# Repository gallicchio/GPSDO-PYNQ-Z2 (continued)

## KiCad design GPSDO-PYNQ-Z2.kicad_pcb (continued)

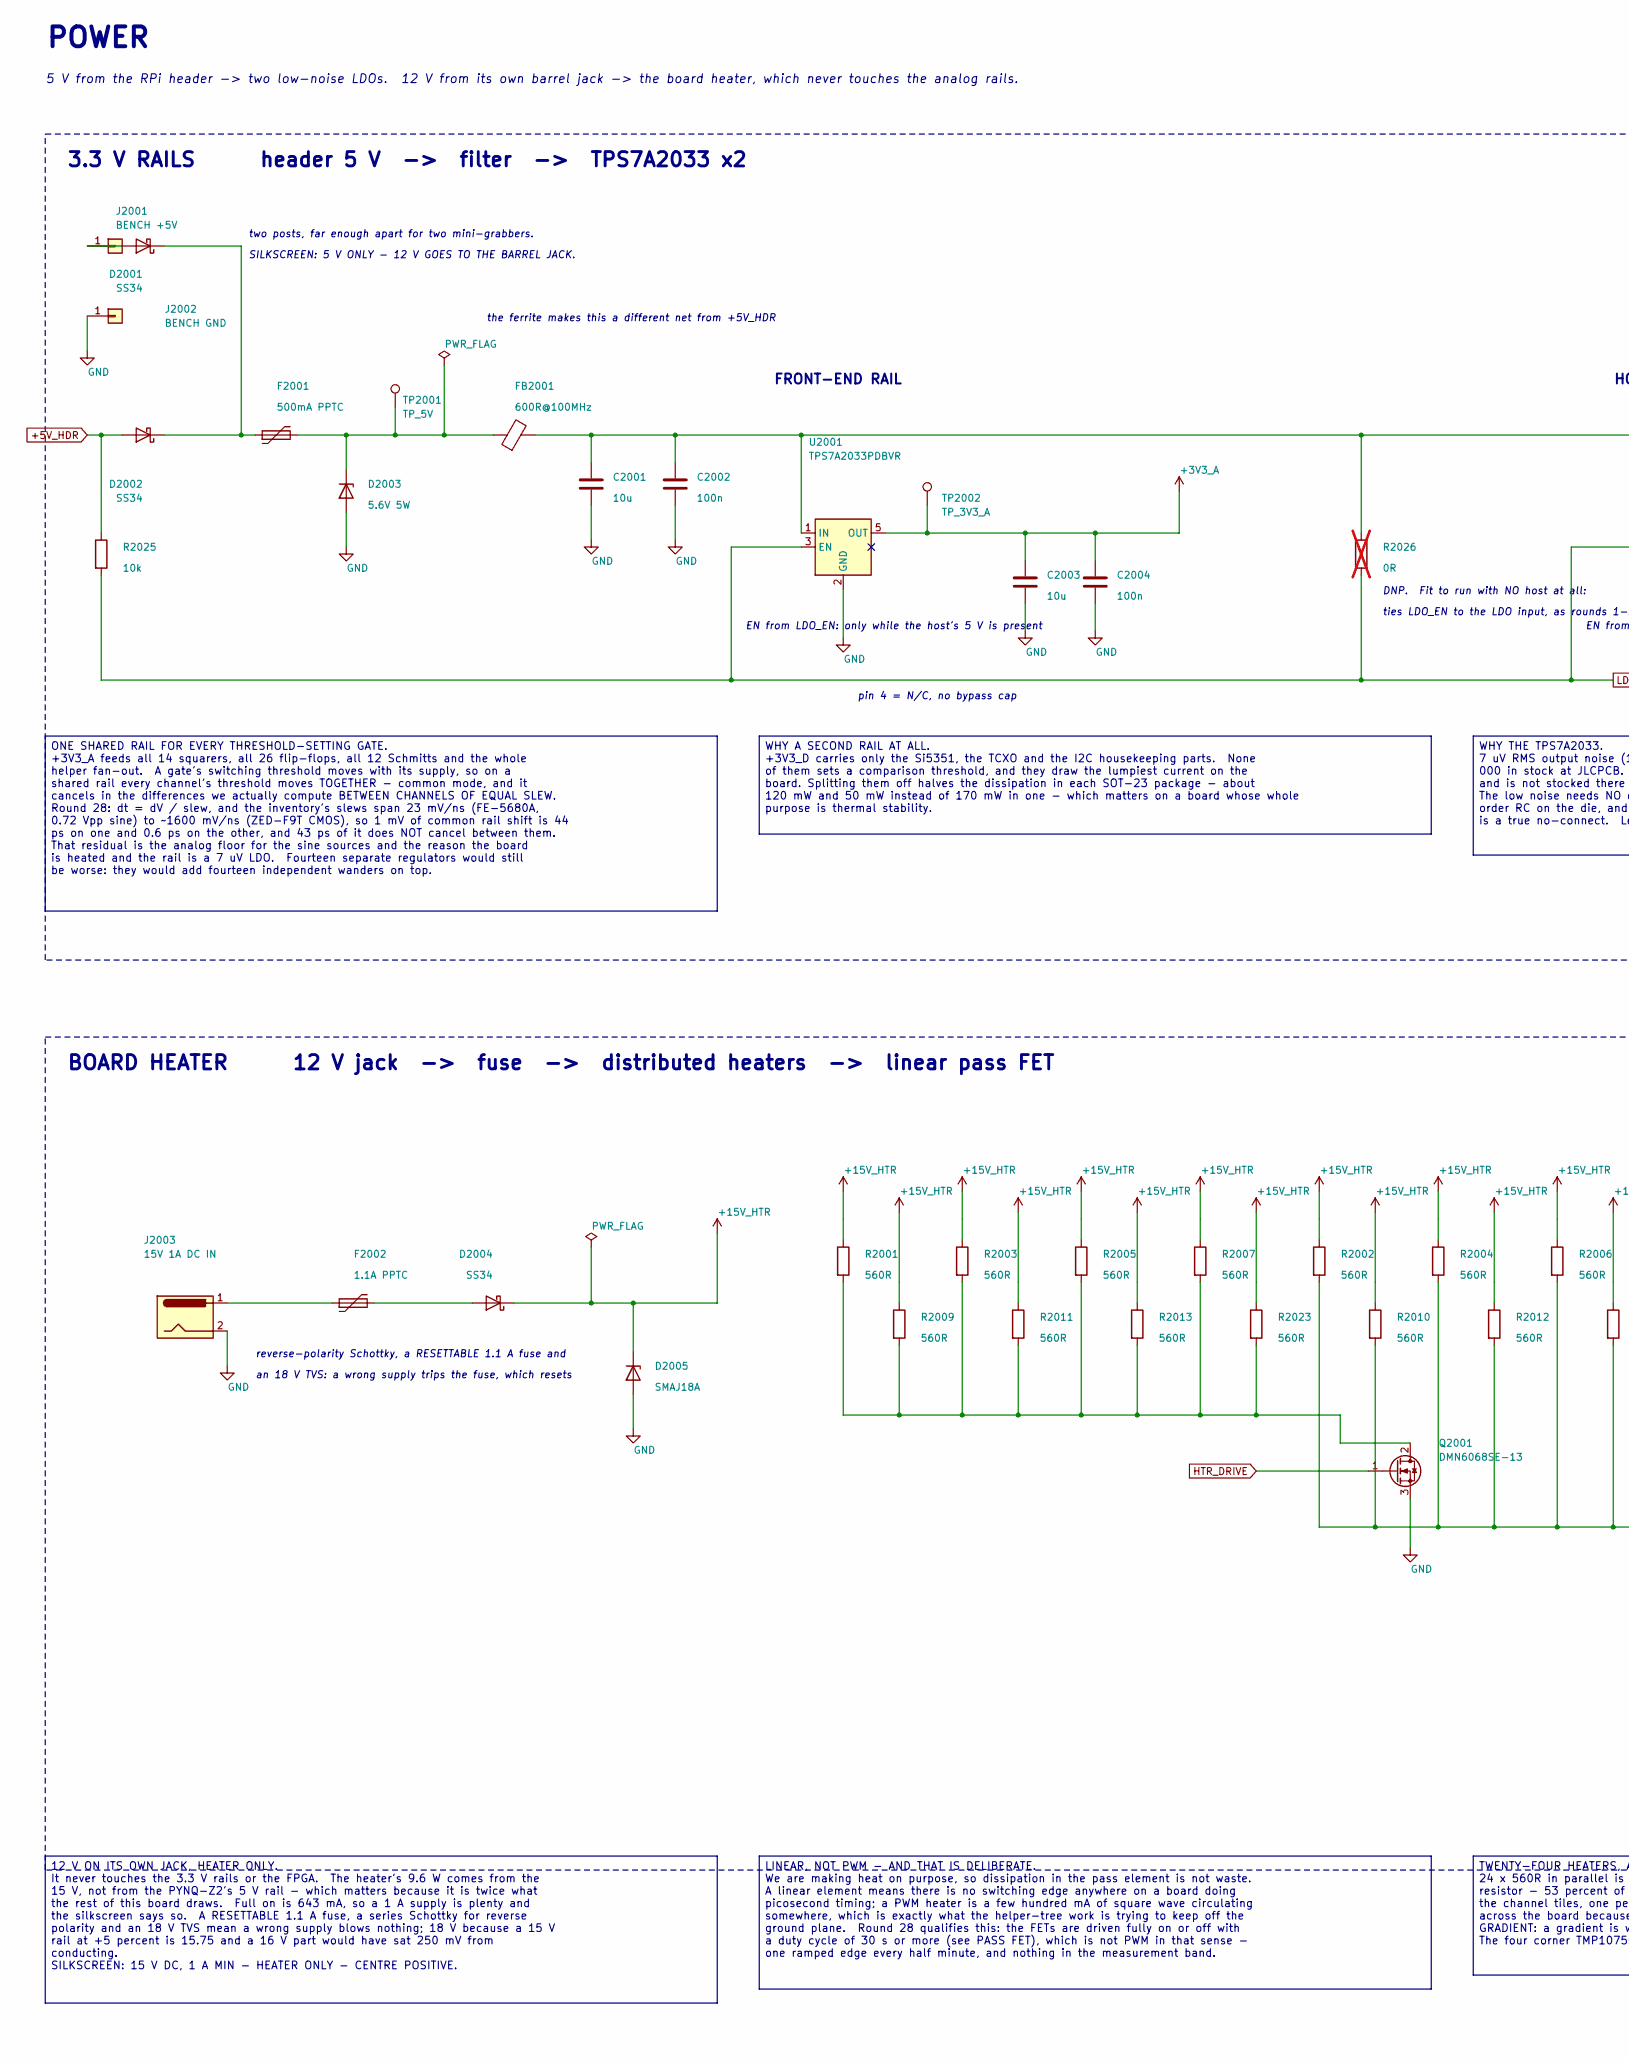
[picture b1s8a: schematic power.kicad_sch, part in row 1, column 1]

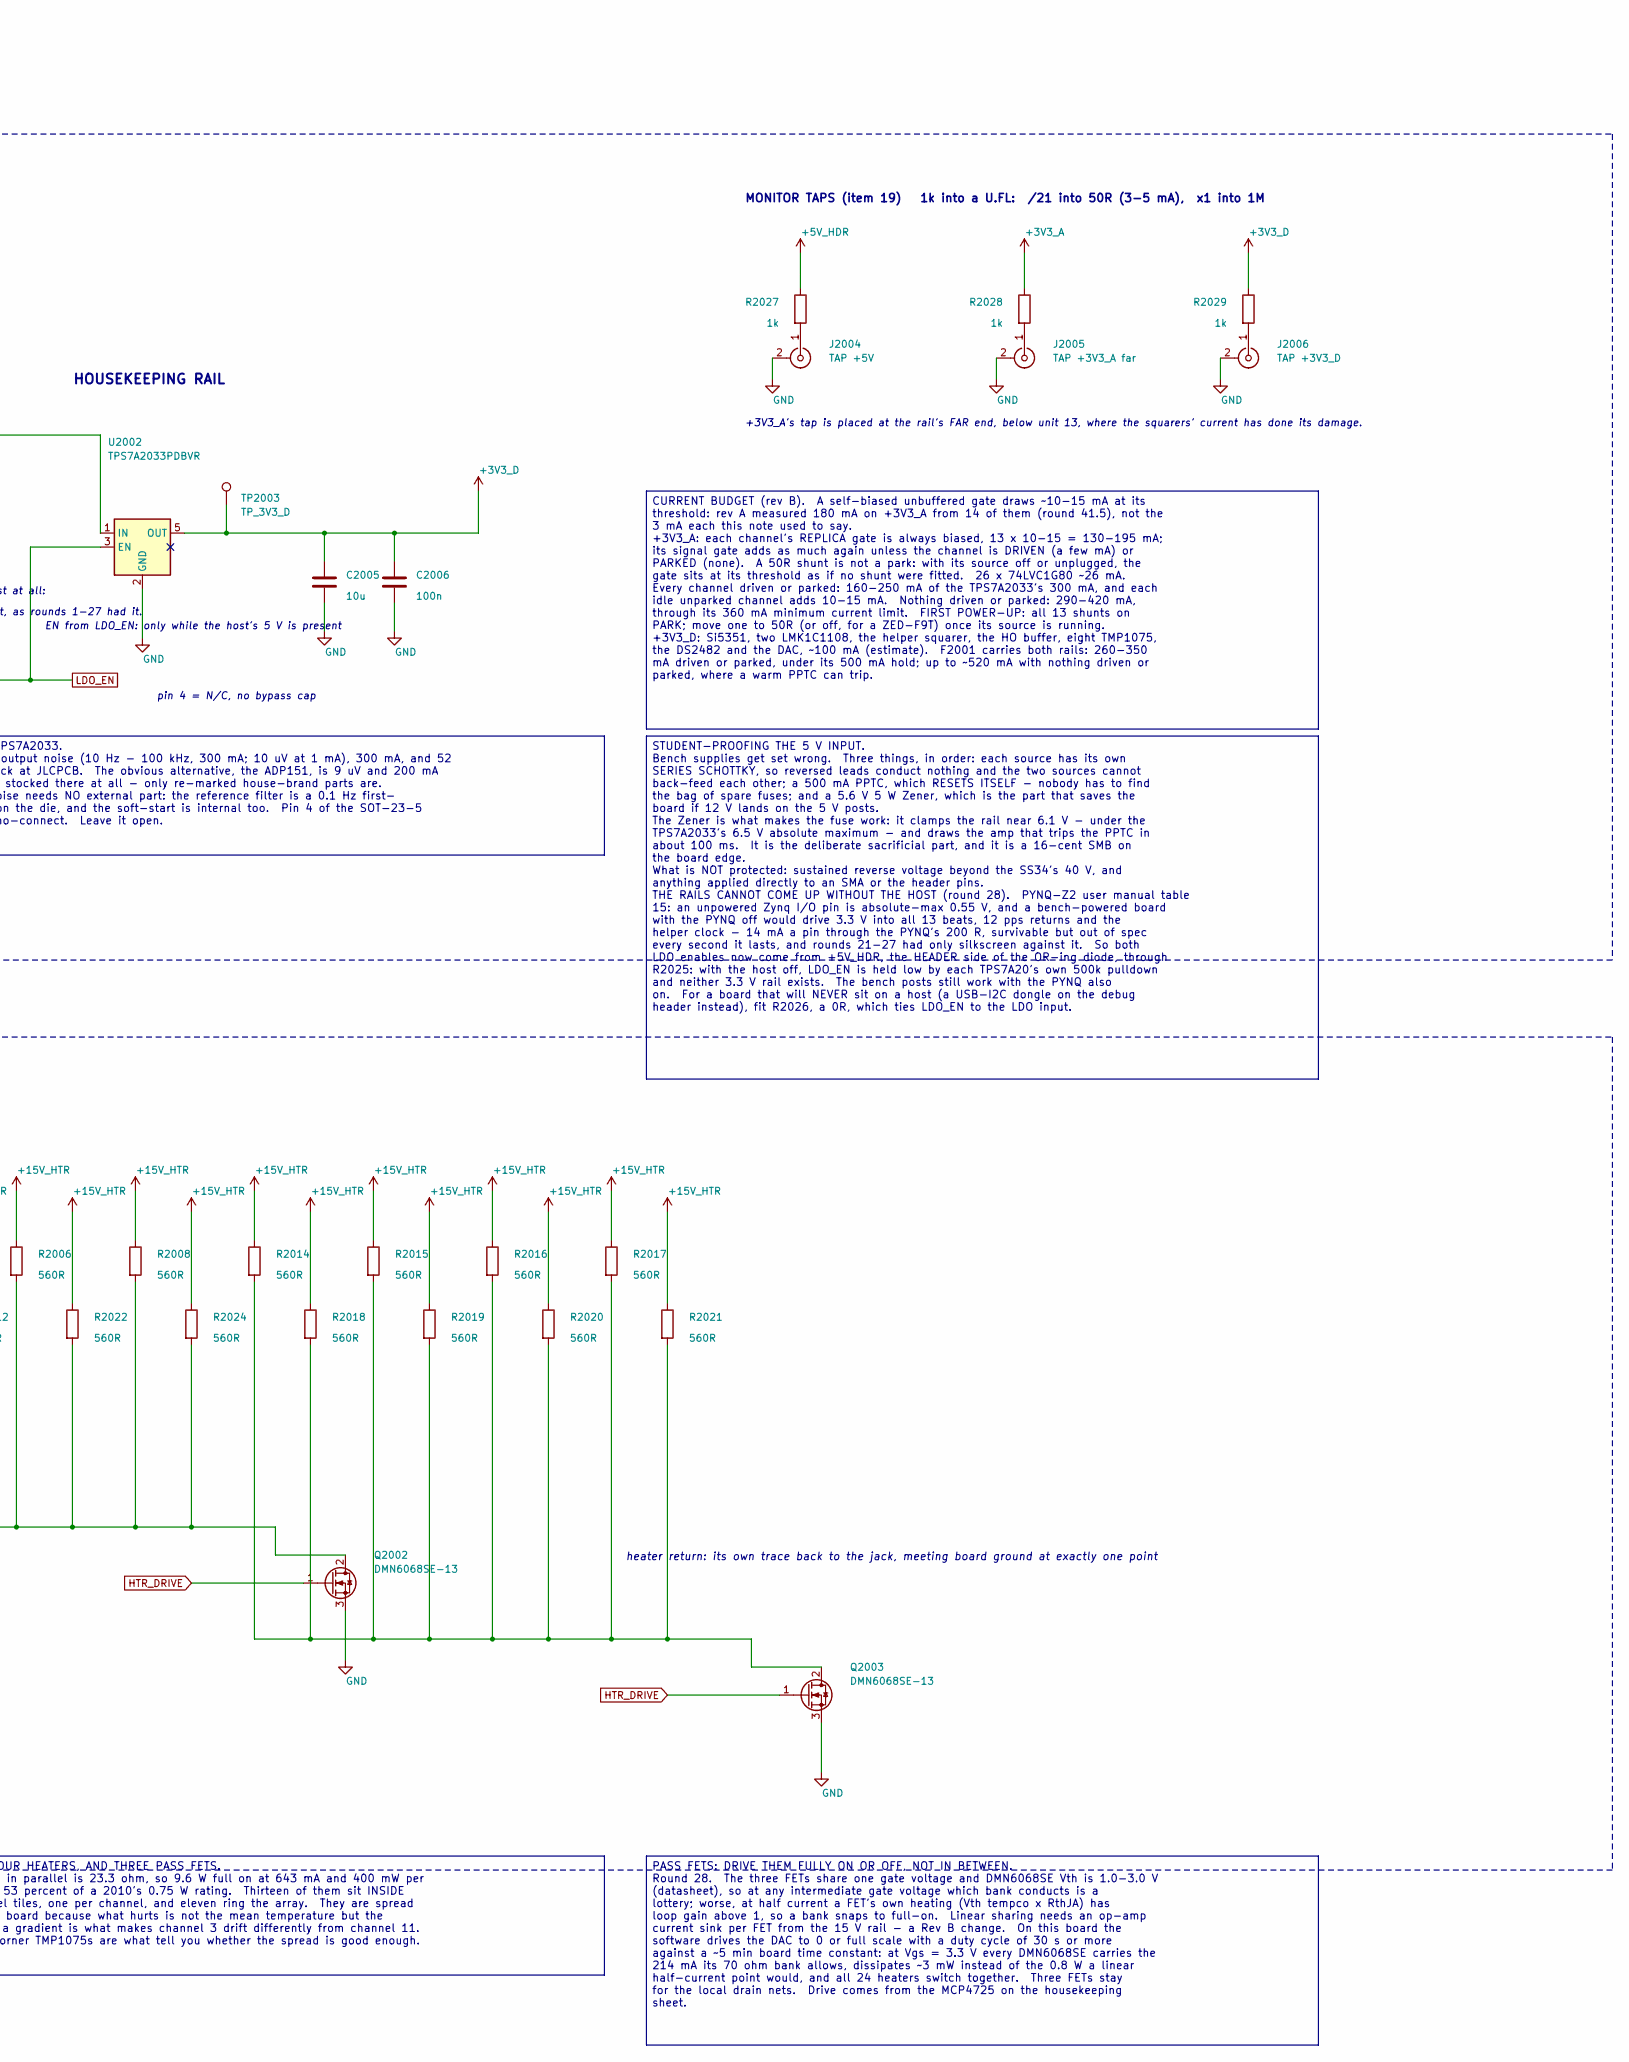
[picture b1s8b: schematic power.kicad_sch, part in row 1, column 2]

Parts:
C2001, C2003, C2005: 10u; C_0805_2012Metric
C2002, C2004, C2006: 100n; C_0805_2012Metric
D2001, D2002, D2004: SS34; D_SMA; LCSC C8678
D2003: 5.6V 5W; D_SMB; LCSC C19077494
D2005: SMAJ18A; D_SMA
F2001: 500mA PPTC; Fuse_1206_3216Metric; LCSC C720075
F2002: 1.1A PPTC; Fuse_1206_3216Metric; LCSC C19108403
FB2001: 600R@100MHz; L_0805_2012Metric
J2001: BENCH +5V; PinHeader_1x01_P2.54mm_Vertical
J2002: BENCH GND; PinHeader_1x01_P2.54mm_Vertical
J2003: 15V 1A DC IN; BarrelJack_Horizontal; LCSC C720557
J2004: TAP +5V; U.FL_Hirose_U.FL-R-SMT-1_Vertical; LCSC C88374
J2005: TAP +3V3_A far; U.FL_Hirose_U.FL-R-SMT-1_Vertical; LCSC C88374
J2006: TAP +3V3_D; U.FL_Hirose_U.FL-R-SMT-1_Vertical; LCSC C88374
Q2001, Q2002, Q2003: DMN6068SE-13; SOT-223-3_TabPin2; LCSC C209902
R2001, R2002, R2003, R2004, R2005, R2006, R2007, R2008, R2009, R2010, R2011, R2012, R2013, R2014, R2015, R2016, R2017, R2018, R2019, R2020, R2021, R2022, R2023, R2024: 560R; R_2010_5025Metric
R2025: 10k; R_0805_2012Metric
R2026: 0R; R_0805_2012Metric; not fitted
R2027, R2028, R2029: 1k; R_0805_2012Metric
TP2001: TP_5V; TestPoint_Pad_D1.5mm
TP2002: TP_3V3_A; TestPoint_Pad_D1.5mm
TP2003: TP_3V3_D; TestPoint_Pad_D1.5mm
U2001, U2002: TPS7A2033PDBVR; SOT-23-5; LCSC C2862740

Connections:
+3V3_A: C2003.1, C2004.1, R2028.1, TP2002.1, U2001.5 (OUT); also elsewhere on the board
+3V3_D: C2005.1, C2006.1, R2029.1, TP2003.1, U2002.5 (OUT); also elsewhere on the board
+5V_HDR: D2002.2 (A), R2025.1, R2027.1; also elsewhere on the board
GND: C2001.2, C2002.2, C2003.2, C2004.2, C2005.2, C2006.2, D2003.2 (A), D2005.2 (A), J2002.1, J2003.2, J2004.2 (Ext), J2005.2 (Ext), J2006.2 (Ext), Q2001.3 (S), Q2002.3 (S), Q2003.3 (S), U2001.2 (GND), U2002.2 (GND); also elsewhere on the board
HTR_DRIVE: Q2001.1 (G), Q2002.1 (G), Q2003.1 (G); also elsewhere on the board
LDO_EN: R2025.2, R2026.2, U2001.3 (EN), U2002.3 (EN)
unnamed: D2001.2 (A), J2001.1
unnamed: D2001.1 (K), D2002.1 (K), F2001.1
unnamed: D2004.2 (A), F2002.2
unnamed: F2002.1, J2003.1
unnamed: J2004.1 (In), R2027.2
unnamed: J2005.1 (In), R2028.2
unnamed: J2006.1 (In), R2029.2
unnamed: Q2001.2 (D), R2001.2, R2003.2, R2005.2, R2007.2, R2009.2, R2011.2, R2013.2, R2023.2
unnamed: Q2002.2 (D), R2002.2, R2004.2, R2006.2, R2008.2, R2010.2, R2012.2, R2022.2, R2024.2
unnamed: Q2003.2 (D), R2014.2, R2015.2, R2016.2, R2017.2, R2018.2, R2019.2, R2020.2, R2021.2
unnamed: C2001.1, C2002.1, FB2001.2, R2026.1, U2001.1 (IN), U2002.1 (IN)

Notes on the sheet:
pin 4 = N/C, no bypass cap
two posts, far enough apart for two mini-grabbers.
SILKSCREEN: 5 V ONLY - 12 V GOES TO THE BARREL JACK.
POWER
5 V from the RPi header -> two low-noise LDOs. 12 V from its own barrel jack -> the board heater, which never touches the analog rails.
+3V3_A's tap is placed at the rail's FAR end, below unit 13, where the squarers' current has done its damage.
an 18 V TVS: a wrong supply trips the fuse, which resets
EN from LDO_EN: only while the host's 5 V is present
3.3 V RAILS header 5 V -> filter -> TPS7A2033 x2
DNP. Fit to run with NO host at all:
reverse-polarity Schottky, a RESETTABLE 1.1 A fuse and
MONITOR TAPS (item 19) 1k into a U.FL: /21 into 50R (3-5 mA), x1 into 1M
HOUSEKEEPING RAIL
heater return: its own trace back to the jack, meeting board ground at exactly one point
the ferrite makes this a different net from +5V_HDR
FRONT-END RAIL
ties LDO_EN to the LDO input, as rounds 1-27 had it.
BOARD HEATER 12 V jack -> fuse -> distributed heaters -> linear pass FET
CURRENT BUDGET (rev B). A self-biased unbuffered gate draws ~10-15 mA at its threshold: rev A measured 180 mA on +3V3_A from 14 of them (round 41.5), not the 3 mA each this note used to say. +3V3_A: each channel's REPLICA gate is always biased, 13 x 10-15 = 130-195 mA; its signal gate adds as much 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
PASS FETS: DRIVE THEM FULLY ON OR OFF, NOT IN BETWEEN. Round 28. The three FETs share one gate voltage and DMN6068SE Vth is 1.0-3.0 V (datasheet), so at any intermediate gate voltage which bank conducts is a lottery; worse, at half current a FET's own heating (Vth tempco x RthJA) has loop gain abov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
TWENTY-FOUR HEATERS, AND THREE PASS FETS. 24 x 560R in parallel is 23.3 ohm, so 9.6 W full on at 643 mA and 400 mW per resistor - 53 percent of a 2010's 0.75 W rating. Thirteen of them sit INSIDE the channel tiles, one per channel, and eleven ring the array. They are spread across the board because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
LINEAR, NOT PWM - AND THAT IS DELIBERATE. We are making heat on purpose, so dissipation in the pass element is not waste. A linear element means there is no switching edge anywhere on a board doing picosecond timing; a PWM heater is a few hundred mA of square wave circulating somewhere, which is ex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
STUDENT-PROOFING THE 5 V INPUT. Bench supplies get set wrong. Three things, in order: each source has its own SERIES SCHOTTKY, so reversed leads conduct nothing and the two sources cannot back-feed each other; a 500 mA PPTC, which RESETS ITSELF - nobody has to find the bag of spare fuses; and a 5.6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
ONE SHARED RAIL FOR EVERY THRESHOLD-SETTING GATE. +3V3_A feeds all 14 squarers, all 26 flip-flops, all 12 Schmitts and the whole helper fan-out. A gate's switching threshold moves with its supply, so on a shared rail every channel's threshold moves TOGETHER - common mode, and it cancels in the diff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
WHY THE TPS7A2033. 7 uV RMS output noise (10 Hz - 100 kHz, 300 mA; 10 uV at 1 mA), 300 mA, and 52 000 in stock at JLCPCB. The obvious alternative, the ADP151, is 9 uV and 200 mA and is not stocked there at all - only re-marked house-brand parts are. The low noise needs NO external part: the referen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
WHY A SECOND RAIL AT ALL. +3V3_D carries only the Si5351, the TCXO and the I2C housekeeping parts. None of them sets a comparison threshold, and they draw the lumpiest current on the board. Splitting them off halves the dissipation in each SOT-23 package - about 120 mW and 50 mW instead of 170 mW i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
12 V ON ITS OWN JACK, HEATER ONLY. It never touches the 3.3 V rails or the FPGA. The heater's 9.6 W comes from the 15 V, not from the PYNQ-Z2's 5 V rail - which matters because it is twice what the rest of this board draws. Full on is 643 mA, so a 1 A supply is plenty and the silkscreen says so. A 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

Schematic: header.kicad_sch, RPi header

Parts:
J4001: 2x20 socket 2.54mm; RPiHeader_2x20_Socket_Underside; LCSC C2977589

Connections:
+5V_HDR: J4001.2, J4001.4; also elsewhere on the board
BEAT_00: J4001.23; also elsewhere on the board
BEAT_01: J4001.7; also elsewhere on the board
BEAT_02: J4001.27; also elsewhere on the board
BEAT_03: J4001.11; also elsewhere on the board
BEAT_04: J4001.29; also elsewhere on the board
BEAT_05: J4001.13; also elsewhere on the board
BEAT_06: J4001.31; also elsewhere on the board
BEAT_07: J4001.15; also elsewhere on the board
BEAT_08: J4001.33; also elsewhere on the board
BEAT_09: J4001.19; also elsewhere on the board
BEAT_10: J4001.35; also elsewhere on the board
BEAT_11: J4001.21; also elsewhere on the board
BEAT_12: J4001.37; also elsewhere on the board
GND: J4001.6, J4001.9, J4001.14, J4001.20, J4001.25, J4001.30, J4001.34, J4001.39; also elsewhere on the board
HELPER_CLK: J4001.18; also elsewhere on the board
I2C_SCL: J4001.5; also elsewhere on the board
I2C_SDA: J4001.3; also elsewhere on the board
PPS_00: J4001.26; also elsewhere on the board
PPS_01: J4001.8; also elsewhere on the board
PPS_02: J4001.28; also elsewhere on the board
PPS_03: J4001.10; also elsewhere on the board
PPS_04: J4001.32; also elsewhere on the board
PPS_05: J4001.12; also elsewhere on the board
PPS_06: J4001.36; also elsewhere on the board
PPS_07: J4001.16; also elsewhere on the board
PPS_08: J4001.38; also elsewhere on the board
PPS_09: J4001.22; also elsewhere on the board
PPS_10: J4001.40; also elsewhere on the board
PPS_11: J4001.24; also elsewhere on the board

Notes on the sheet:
C20 IO_L1P_T0_AD0P_35 unit 6 pps
B20 IO_L1N_T0_AD0N_35 unit 5 pps
pin 1 3V3 from the host - NOT CONNECTED
U19 IO_L12N_T1_MRCC_34 unit 1 pps
W9 IO_L16N_T2_13 unit 13 beat
V6 IO_L22P_T3_13 unit 2 pps
Y16 IO_L7P_T1_34 unit 3 beat
F19 IO_L15P_T2_DQS_AD12P_35 unit 12 pps
U8 IO_L17N_T2_13 unit 8 beat
W8 IO_L15N_T2_DQS_13 unit 9 beat
V7 IO_L11N_T1_SRCC_13 unit 6 beat
Y18 IO_L17P_T2_34 unit 2 beat
V8 IO_L15P_T2_DQS_13 unit 10 beat
Y9 IO_L14P_T2_SRCC_13 unit 11 pps
2x20 female socket on the underside. Pin map taken from TUL_PYNQ_Schematic_R12.pdf sheet 4, cross-checked against Vivado's PIN_FUNC database. Every signal pin has its own 200R series resistor on the PYNQ-Z2.
Y6 IO_L13N_T2_MRCC_13 unit 4 pps
W10 IO_L16P_T2_13 unit 1 beat
V10 IO_L21N_T3_DQS_13 unit 12 beat
W18 IO_L22P_T3_34 I2C SDA - 2k2 pull-up already on PYNQ-Z2
pin 17 3V3 from the host - NOT CONNECTED
Y19 IO_L17N_T2_34 unit 5 beat
U18 IO_L12P_T1_MRCC_34 unit 7 beat
Y8 IO_L14N_T2_SRCC_13 unit 11 beat
U7 IO_L11P_T1_SRCC_13 unit 4 beat
F20 IO_L15N_T2_DQS_AD12N_35 unit 10 pps
Y7 IO_L13P_T2_MRCC_13 HELPER CLOCK -> FPGA (MRCC P, bank 13)
A20 IO_L2N_T0_AD8N_35 unit 9 pps
W19 IO_L22N_T3_34 I2C SCL - 2k2 pull-up already on PYNQ-Z2
B19 IO_L2P_T0_AD8P_35 unit 7 pps
RASPBERRY PI 40-PIN HEADER
W6 IO_L22N_T3_13 unit 8 pps
Y17 IO_L7N_T1_34 unit 3 pps
NO MODIFICATION TO THE PYNQ-Z2 IS NEEDED - BUT PMOD A BECOMES UNUSABLE. This board is designed for a stock PYNQ-Z2. It relies on the 200 ohm series resistor the PYNQ puts in every Raspberry Pi GPIO, and on the 2k2 I2C pull-ups above; both are fitted from the factory and neither should be removed. W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
THE ROW SPLIT IS NOT A COINCIDENCE. After taking pins 3 and 5 for I2C the odd row has exactly 13 signal pins left, and after taking pin 18 for the helper the even row has exactly 12. So every BEAT is on the odd row and every PPS on the even row, which separates the two families across the connector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
THE HELPER GOES IN ON PIN 18. Y7 = rpio_24 = IO_L13P_T2_MRCC_13: an MRCC P-side pin in bank 13, the best clock input on the board. The same physical pin is a dedicated PCLKT6_1 primary clock input on an Icepi Zero, so one choice serves both platforms. Pin 31 (U18, MRCC bank 34) is the fallback.
PIN 1 AND PIN 17 ARE LEFT UNCONNECTED. Both are the host's 3.3 V. We make our own 3.3 V from the header's 5 V, and not bridging to the host's rail means we cannot back-feed it. The TUL user manual's Table 22 shows pin 1 as GROUND; the schematic shows 3V3, and the schematic is right. Leaving the pin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
PIN 13 IS REAL AND IS MISSING FROM THE STOCK XDC. Net RPIO_27_R, package pin V7, IO_L11N_T1_SRCC_13, fed through R87 (200R 1%). The widely-circulated pynq-z2.xdc simply omits it, so anyone counting from that file finds 26 usable pins where the board has 28. On this board it carries BEAT_05. Add the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
2k2 PULL-UPS ARE ALREADY FITTED ON THE PYNQ-Z2 on header pins 3, 5, 27 and 28 (R305-R308), which is the standard Raspberry Pi I2C arrangement. Do not add more on this board. Pins 27 and 28 carry BEAT_02 and PPS_02; a 2k2 pull-up on a push-pull LVC output is 1.5 mA and harmless, and any rise/fall as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

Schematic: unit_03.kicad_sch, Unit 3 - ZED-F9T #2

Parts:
C301: 10n C0G; C_0805_2012Metric
C302, C304, C306, C308: 100n; C_0805_2012Metric
C303, C305, C307, C309: 10n; C_0805_2012Metric
D301: BAV99; SOT-23; LCSC C916421; not fitted
J301: 10MHz IN; SMA_Vertical_THT_Universal; LCSC C496549
J302: 1pps IN; SMA_Vertical_THT_Universal; LCSC C496549
J303: TAP IN; U.FL_Hirose_U.FL-R-SMT-1_Vertical; LCSC C88374
J304: TAP SQ; U.FL_Hirose_U.FL-R-SMT-1_Vertical; LCSC C88374
JP301: 50R/PARK; PinHeader_1x03_P2.54mm_Vertical
R301: 51R 1%; R_0805_2012Metric
R302: 0R; R_0805_2012Metric
R303: 2k2; R_0805_2012Metric
R304: 330R; R_0805_2012Metric
R305: 1M 1%; R_0805_2012Metric
R306: 51R; R_0805_2012Metric; not fitted
R307, R321, R323: 1k; R_0805_2012Metric
R308: 10k; R_0805_2012Metric
R322: 100k; R_0805_2012Metric
R351, R352, R353, R354: 4R7; R_0805_2012Metric
TP301: TP_IN; TestPoint_Pad_D1.5mm
TP302: TP_SQ; TestPoint_Pad_D1.5mm
TP303: TP_BEAT; TestPoint_Pad_D1.5mm
TP304: TP_PPS; TestPoint_Pad_D1.5mm
U301: 74LVC2GU04; SOT-363_SC-70-6; LCSC C116660
U302, U303: 74LVC1G80; SOT-23-5; LCSC C42879
U304: 74LVC1G17; SOT-23-5; LCSC C7836

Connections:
+3V3_A: D301.1 (K), R351.1, R352.1, R353.1, R354.1; also elsewhere on the board
/Unit 03/PARK: JP301.3, R322.2
/Unit 03/REPLICA: R305.2, U301.3 (2A), U301.4 (2Y)
BEAT_02: TP303.1, U303.4 (~Q); also elsewhere on the board
GND: C302.2, C303.2, C304.2, C305.2, C306.2, C307.2, C308.2, C309.2, D301.2 (A), J301.2 (Ext), J302.2 (Ext), J303.2 (Ext), J304.2 (Ext), JP301.2, R303.2, R306.2, R308.2, U301.2 (GND), U302.3 (GND), U303.3 (GND), U304.3 (GND); also elsewhere on the board
HCLK_02: U302.2 (C), U303.2 (C); also elsewhere on the board
unnamed: C301.1, R302.2, R303.1, R321.2
unnamed: C301.2, D301.3 (K), R304.1
unnamed: J301.1 (In), R301.1, R302.1, TP301.1
unnamed: J302.1 (In), R306.1, R307.1
unnamed: J303.1 (In), R321.1
unnamed: J304.1 (In), R323.1
unnamed: JP301.1, R301.2
unnamed: R307.2, R308.1, U304.2
unnamed: R304.2, R305.1, R322.1, TP302.1, U301.1 (1A)
unnamed: R323.2, U301.6 (1Y), U302.1 (D)
unnamed: C302.1, C303.1, R351.2, U301.5 (VCC)
unnamed: C304.1, C305.1, R352.2, U302.5 (VCC)
unnamed: U302.4 (~Q), U303.1 (D)
unnamed: C306.1, C307.1, R353.2, U303.5 (VCC)
unnamed: C308.1, C309.1, R354.2, U304.5 (VCC)
PPS_02: TP304.1, U304.4; also elsewhere on the board

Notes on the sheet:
UNIT 3 - ZED-F9T #2
out: PPS_02, one rising edge per second, 0/3.3 V, straight to the RPi header
bounds the current from a
DC level when nothing
neither = a driven, unterminated input
1k/10k suits a 3.3 V and a 5 V
10 MHz DDMTD front end + 1 pps front end. Every unit sheet has this same layout; only the names, the per-channel population and the expected levels differ.
1 pps CHANNEL divide -> Schmitt -> straight to the FPGA
10 MHz DDMTD CHANNEL terminate -> AC couple -> square -> sample -> retime
supply pin: it decides at its threshold, not 70 mV off (item 18).
AC couple
1-2 = 50 ohm terminate (ON except ZED-F9T)
jumper is off, and sets the
DNP: nothing here drives 50 ohm
is plugged in
OUT BEAT_02 -> sheet 'RPi header' OUT PPS_02 -> sheet 'RPi header' IN HELPER_FANOUT <- sheet 'Helper'
HCLK_02: 10.0012 MHz, 0/3.3 V, this channel's own length-matched branch off the fan-out
its own threshold; the 1M carries that to half 1. One die, one
2-3 = PARK: source off or unplugged (not 50R)
REPLICA BIAS. Half 2, its input tied to its output, sits at
pps alike, so no channel differs
high-Z source when the
into FF1.D: 0/3.3 V CMOS at 10 MHz, edges ~1-2 ns
out of FF2: BEAT_02, ~1234 Hz square, 0/3.3 V - its EDGE TIME is the measurement
DNP clamp: fit only for an unterminated hot source
THE SAMPLING FLIP-FLOP (FF1) IS DELIBERATELY ALLOWED TO GO METASTABLE - that is measurement. Never put a synchronizer in front of it. THE RETIMER (FF2) re-clocks on the next helper edge, so what leaves the board is always a clean transition aligned to a helper edge. It costs exactly one helper cycl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
AT THE INPUT NODE, before the coupling cap 3.30 Vpp, center 1.65 V UNTERMINATED load 2k2 only (1.5 mA peak)
THE 50R TERM, THE JUMPER SHIPS REMOVED. Fit only if the source drives 50 ohm. A ZED-F9T is DESTROYED by fitting it: its TIMEPULSE pin is 5 mA absolute maximum and 3.3 V into 50R asks for 66 mA. Conversely, leaving it out on an 8 Vpp open-circuit source floats the gate input to about +7.4 V, over th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
DC-COUPLED, DELIBERATELY. The pps widths in this inventory span 1 us (FE-5680A) to 100 ms (ZED-F9T, LBE-1421), and no single AC-coupling RC covers five decades: a 10n/100k network passes the 1 us pulse and droops away to nothing 1% into the 100 ms one. The 1k/10k divider is fitted on EVERY pps chan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
SCHMITT BUFFER, NOT AN INVERTER. Hysteresis is wrong for the 10 MHz path - it moves the trigger off the zero crossing and turns amplitude into phase - but it is right here: a pps is a rare, fast, possibly noisy edge on a long cable, which is the chatter case hysteresis exists for. No self-bias: a S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
AFTER THE 1k / 10k 3.00 V or 4.55 V at the Schmitt input
AT THE INPUT 3.3 V or 5 V pps DC coupled, no droop
AT THE GATE, at TP_SQ 3.30 Vpp, center 1.65 V 0.00 to 3.30 V slew ~1650 mV/ns
WHY THE 74LVC2GU04 (rev B) TWO unbuffered inverters on one die: half 1 squares, half 2 is its replica bias (item 18). U = UNBUFFERED, one gain stage: three cascaded stages inside a feedback loop oscillate, one cannot. LVC = 5.5 V tolerant inputs on a 3.3 V rail, so a 5 V source survives contact, an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
WHY THE 74LVC1G80 The simplest D flip-flop there is: D, CLK, one output and the two rails, and nothing else. No preset and no clear, so there is no asynchronous input that could reset a sampler which must never be reset, and nothing to tie off. Same 74LVC family and the same SOT-23-5 footprint as t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
PER-CHANNEL NOTE NEVER fit the 50R TERM jumper - see unit 2
THE BAV99 CLAMP IS DNP. Fit only on a channel you will run UNTERMINATED with a source above about 6 Vpp open circuit. It is not fitted by default because its reverse leakage flows in the 1M self-bias resistor: 10 nA is 10 mV of bias shift, leakage roughly doubles every 10 degC, and at ~1650 mV/ns t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

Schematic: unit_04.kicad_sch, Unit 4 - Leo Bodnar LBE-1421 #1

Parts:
C401: 10n C0G; C_0805_2012Metric
C402, C404, C406, C408: 100n; C_0805_2012Metric
C403, C405, C407, C409: 10n; C_0805_2012Metric
D401: BAV99; SOT-23; LCSC C916421; not fitted
J401: 10MHz IN; SMA_Vertical_THT_Universal; LCSC C496549
J402: 1pps IN; SMA_Vertical_THT_Universal; LCSC C496549
J403: TAP IN; U.FL_Hirose_U.FL-R-SMT-1_Vertical; LCSC C88374
J404: TAP SQ; U.FL_Hirose_U.FL-R-SMT-1_Vertical; LCSC C88374
JP401: 50R/PARK; PinHeader_1x03_P2.54mm_Vertical
R401: 51R 1%; R_0805_2012Metric
R402: 0R; R_0805_2012Metric
R403: 2k2; R_0805_2012Metric
R404: 330R; R_0805_2012Metric
R405: 1M 1%; R_0805_2012Metric
R406: 51R; R_0805_2012Metric; not fitted
R407, R421, R423: 1k; R_0805_2012Metric
R408: 10k; R_0805_2012Metric
R422: 100k; R_0805_2012Metric
R451, R452, R453, R454: 4R7; R_0805_2012Metric
TP401: TP_IN; TestPoint_Pad_D1.5mm
TP402: TP_SQ; TestPoint_Pad_D1.5mm
TP403: TP_BEAT; TestPoint_Pad_D1.5mm
TP404: TP_PPS; TestPoint_Pad_D1.5mm
U401: 74LVC2GU04; SOT-363_SC-70-6; LCSC C116660
U402, U403: 74LVC1G80; SOT-23-5; LCSC C42879
U404: 74LVC1G17; SOT-23-5; LCSC C7836

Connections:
+3V3_A: D401.1 (K), R451.1, R452.1, R453.1, R454.1; also elsewhere on the board
/Unit 04/PARK: JP401.3, R422.2
/Unit 04/REPLICA: R405.2, U401.3 (2A), U401.4 (2Y)
BEAT_03: TP403.1, U403.4 (~Q); also elsewhere on the board
GND: C402.2, C403.2, C404.2, C405.2, C406.2, C407.2, C408.2, C409.2, D401.2 (A), J401.2 (Ext), J402.2 (Ext), J403.2 (Ext), J404.2 (Ext), JP401.2, R403.2, R406.2, R408.2, U401.2 (GND), U402.3 (GND), U403.3 (GND), U404.3 (GND); also elsewhere on the board
HCLK_03: U402.2 (C), U403.2 (C); also elsewhere on the board
unnamed: J401.1 (In), R401.1, R402.1, TP401.1
unnamed: J402.1 (In), R406.1, R407.1
unnamed: J403.1 (In), R421.1
unnamed: J404.1 (In), R423.1
unnamed: JP401.1, R401.2
unnamed: R407.2, R408.1, U404.2
unnamed: R404.2, R405.1, R422.1, TP402.1, U401.1 (1A)
unnamed: R423.2, U401.6 (1Y), U402.1 (D)
unnamed: C402.1, C403.1, R451.2, U401.5 (VCC)
unnamed: C404.1, C405.1, R452.2, U402.5 (VCC)
unnamed: U402.4 (~Q), U403.1 (D)
unnamed: C406.1, C407.1, R453.2, U403.5 (VCC)
unnamed: C408.1, C409.1, R454.2, U404.5 (VCC)
PPS_03: TP404.1, U404.4; also elsewhere on the board

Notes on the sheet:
out: PPS_03, one rising edge per second, 0/3.3 V, straight to the RPi header
2-3 = PARK: an unused channel, quiet
10 MHz DDMTD front end + 1 pps front end. Every unit sheet has this same layout; only the names, the per-channel population and the expected levels differ.
DNP: nothing here drives 50 ohm
HCLK_03: 10.0012 MHz, 0/3.3 V, this channel's own length-matched branch off the fan-out
high-Z source when the
1-2 = 50 ohm terminate (ON except ZED-F9T)
UNIT 4 - Leo Bodnar LBE-1421 #1
10 MHz DDMTD CHANNEL terminate -> AC couple -> square -> sample -> retime
jumper is off, and sets the
bounds the current from a
neither = a driven, unterminated input
its own threshold; the 1M carries that to half 1. One die, one
REPLICA BIAS. Half 2, its input tied to its output, sits at
supply pin: it decides at its threshold, not 70 mV off (item 18).
out of FF2: BEAT_03, ~1234 Hz square, 0/3.3 V - its EDGE TIME is the measurement
pps alike, so no channel differs
DC level when nothing
DNP clamp: fit only for an unterminated hot source
into FF1.D: 0/3.3 V CMOS at 10 MHz, edges ~1-2 ns
OUT BEAT_03 -> sheet 'RPi header' OUT PPS_03 -> sheet 'RPi header' IN HELPER_FANOUT <- sheet 'Helper'
1 pps CHANNEL divide -> Schmitt -> straight to the FPGA
1k/10k suits a 3.3 V and a 5 V
is plugged in
AC couple
DC-COUPLED, DELIBERATELY. The pps widths in this inventory span 1 us (FE-5680A) to 100 ms (ZED-F9T, LBE-1421), and no single AC-coupling RC covers five decades: a 10n/100k network passes the 1 us pulse and droops away to nothing 1% into the 100 ms one. The 1k/10k divider is fitted on EVERY pps chan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
WHY THE 74LVC2GU04 (rev B) TWO unbuffered inverters on one die: half 1 squares, half 2 is its replica bias (item 18). U = UNBUFFERED, one gain stage: three cascaded stages inside a feedback loop oscillate, one cannot. LVC = 5.5 V tolerant inputs on a 3.3 V rail, so a 5 V source survives contact, an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
WHY THE 74LVC1G80 The simplest D flip-flop there is: D, CLK, one output and the two rails, and nothing else. No preset and no clear, so there is no asynchronous input that could reset a sampler which must never be reset, and nothing to tie off. Same 74LVC family and the same SOT-23-5 footprint as t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
AT THE INPUT 3.3 V or 5 V pps DC coupled, no droop
AT THE INPUT NODE, before the coupling cap 1.64 Vpp, center 0.82 V TERMINATED load 51R || 2k2 = 49.8 ohm
SCHMITT BUFFER, NOT AN INVERTER. Hysteresis is wrong for the 10 MHz path - it moves the trigger off the zero crossing and turns amplitude into phase - but it is right here: a pps is a rare, fast, possibly noisy edge on a long cable, which is the chatter case hysteresis exists for. No self-bias: a S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
THE BAV99 CLAMP IS DNP. Fit only on a channel you will run UNTERMINATED with a source above about 6 Vpp open circuit. It is not fitted by default because its reverse leakage flows in the 1M self-bias resistor: 10 nA is 10 mV of bias shift, leakage roughly doubles every 10 degC, and at ~820 mV/ns th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
AT THE GATE, at TP_SQ 1.64 Vpp, center 1.65 V 0.83 to 2.47 V slew ~820 mV/ns
THE SAMPLING FLIP-FLOP (FF1) IS DELIBERATELY ALLOWED TO GO METASTABLE - that is measurement. Never put a synchronizer in front of it. THE RETIMER (FF2) re-clocks on the next helper edge, so what leaves the board is always a clean transition aligned to a helper edge. It costs exactly one helper cycl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
AFTER THE 1k / 10k 3.00 V or 4.55 V at the Schmitt input
THE 50R TERM, THE JUMPER SHIPS REMOVED. Fit only if the source drives 50 ohm. A ZED-F9T is DESTROYED by fitting it: its TIMEPULSE pin is 5 mA absolute maximum and 3.3 V into 50R asks for 66 mA. Conversely, leaving it out on an 8 Vpp open-circuit source floats the gate input to about +7.4 V, over th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

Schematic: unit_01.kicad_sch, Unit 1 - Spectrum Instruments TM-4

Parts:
C101: 10n C0G; C_0805_2012Metric
C102, C104, C106, C108: 100n; C_0805_2012Metric
C103, C105, C107, C109: 10n; C_0805_2012Metric
D101: BAV99; SOT-23; LCSC C916421; not fitted
J101: 10MHz IN; SMA_Vertical_THT_Universal; LCSC C496549
J102: 1pps IN; SMA_Vertical_THT_Universal; LCSC C496549
J103: TAP IN; U.FL_Hirose_U.FL-R-SMT-1_Vertical; LCSC C88374
J104: TAP SQ; U.FL_Hirose_U.FL-R-SMT-1_Vertical; LCSC C88374
JP101: 50R/PARK; PinHeader_1x03_P2.54mm_Vertical
R101: 51R 1%; R_0805_2012Metric
R102: 0R; R_0805_2012Metric
R103: 2k2; R_0805_2012Metric
R104: 330R; R_0805_2012Metric
R105: 1M 1%; R_0805_2012Metric
R106: 51R; R_0805_2012Metric; not fitted
R107, R121, R123: 1k; R_0805_2012Metric
R108: 10k; R_0805_2012Metric
R122: 100k; R_0805_2012Metric
R151, R152, R153, R154: 4R7; R_0805_2012Metric
TP101: TP_IN; TestPoint_Pad_D1.5mm
TP102: TP_SQ; TestPoint_Pad_D1.5mm
TP103: TP_BEAT; TestPoint_Pad_D1.5mm
TP104: TP_PPS; TestPoint_Pad_D1.5mm
U101: 74LVC2GU04; SOT-363_SC-70-6; LCSC C116660
U102, U103: 74LVC1G80; SOT-23-5; LCSC C42879
U104: 74LVC1G17; SOT-23-5; LCSC C7836

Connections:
+3V3_A: D101.1 (K), R151.1, R152.1, R153.1, R154.1; also elsewhere on the board
/Unit 01/PARK: JP101.3, R122.2
/Unit 01/REPLICA: R105.2, U101.3 (2A), U101.4 (2Y)
BEAT_00: TP103.1, U103.4 (~Q); also elsewhere on the board
GND: C102.2, C103.2, C104.2, C105.2, C106.2, C107.2, C108.2, C109.2, D101.2 (A), J101.2 (Ext), J102.2 (Ext), J103.2 (Ext), J104.2 (Ext), JP101.2, R103.2, R106.2, R108.2, U101.2 (GND), U102.3 (GND), U103.3 (GND), U104.3 (GND); also elsewhere on the board
HCLK_00: U102.2 (C), U103.2 (C); also elsewhere on the board
unnamed: C101.1, R102.2, R103.1, R121.2
unnamed: C101.2, D101.3 (K), R104.1
unnamed: J101.1 (In), R101.1, R102.1, TP101.1
unnamed: J102.1 (In), R106.1, R107.1
unnamed: J103.1 (In), R121.1
unnamed: J104.1 (In), R123.1
unnamed: JP101.1, R101.2
unnamed: R107.2, R108.1, U104.2
unnamed: R104.2, R105.1, R122.1, TP102.1, U101.1 (1A)
unnamed: R123.2, U101.6 (1Y), U102.1 (D)
unnamed: C102.1, C103.1, R151.2, U101.5 (VCC)
unnamed: C104.1, C105.1, R152.2, U102.5 (VCC)
unnamed: U102.4 (~Q), U103.1 (D)
unnamed: C106.1, C107.1, R153.2, U103.5 (VCC)
unnamed: C108.1, C109.1, R154.2, U104.5 (VCC)
PPS_00: TP104.1, U104.4; also elsewhere on the board

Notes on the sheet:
supply pin: it decides at its threshold, not 70 mV off (item 18).
HCLK_00: 10.0012 MHz, 0/3.3 V, this channel's own length-matched branch off the fan-out
DNP clamp: fit only for an unterminated hot source
UNIT 1 - Spectrum Instruments TM-4
its own threshold; the 1M carries that to half 1. One die, one
neither = a driven, unterminated input
is plugged in
high-Z source when the
10 MHz DDMTD front end + 1 pps front end. Every unit sheet has this same layout; only the names, the per-channel population and the expected levels differ.
REPLICA BIAS. Half 2, its input tied to its output, sits at
jumper is off, and sets the
out: PPS_00, one rising edge per second, 0/3.3 V, straight to the RPi header
into FF1.D: 0/3.3 V CMOS at 10 MHz, edges ~1-2 ns
2-3 = PARK: source off or unplugged (not 50R)
1-2 = 50 ohm terminate (ON except ZED-F9T)
1 pps CHANNEL divide -> Schmitt -> straight to the FPGA
DC level when nothing
AC couple
out of FF2: BEAT_00, ~1234 Hz square, 0/3.3 V - its EDGE TIME is the measurement
1k/10k suits a 3.3 V and a 5 V
DNP: nothing here drives 50 ohm
bounds the current from a
pps alike, so no channel differs
OUT BEAT_00 -> sheet 'RPi header' OUT PPS_00 -> sheet 'RPi header' IN HELPER_FANOUT <- sheet 'Helper'
10 MHz DDMTD CHANNEL terminate -> AC couple -> square -> sample -> retime
PER-CHANNEL NOTE 8.0 Vpp OPEN CIRCUIT - the hottest source here. The 50R TERM jumper MUST be fitted on this channel: unterminated it floats the gate to about +7.4 V, over the 6.5 V absolute maximum.
THE 50R TERM, THE JUMPER SHIPS REMOVED. Fit only if the source drives 50 ohm. A ZED-F9T is DESTROYED by fitting it: its TIMEPULSE pin is 5 mA absolute maximum and 3.3 V into 50R asks for 66 mA. Conversely, leaving it out on an 8 Vpp open-circuit source floats the gate input to about +7.4 V, over th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
WHY THE 74LVC2GU04 (rev B) TWO unbuffered inverters on one die: half 1 squares, half 2 is its replica bias (item 18). U = UNBUFFERED, one gain stage: three cascaded stages inside a feedback loop oscillate, one cannot. LVC = 5.5 V tolerant inputs on a 3.3 V rail, so a 5 V source survives contact, an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
AT THE INPUT 3.3 V or 5 V pps DC coupled, no droop
AFTER THE 1k / 10k 3.00 V or 4.55 V at the Schmitt input
AT THE INPUT NODE, before the coupling cap 2.00 Vpp, center 0 V TERMINATED load 51R || 2k2 = 49.8 ohm
THE BAV99 CLAMP IS DNP. Fit only on a channel you will run UNTERMINATED with a source above about 6 Vpp open circuit. It is not fitted by default because its reverse leakage flows in the 1M self-bias resistor: 10 nA is 10 mV of bias shift, leakage roughly doubles every 10 degC, and at 63 mV/ns that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
AT THE GATE, at TP_SQ 2.00 Vpp, center 1.65 V 0.65 to 2.65 V slew 63 mV/ns
WHY THE 74LVC1G80 The simplest D flip-flop there is: D, CLK, one output and the two rails, and nothing else. No preset and no clear, so there is no asynchronous input that could reset a sampler which must never be reset, and nothing to tie off. Same 74LVC family and the same SOT-23-5 footprint as t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
SCHMITT BUFFER, NOT AN INVERTER. Hysteresis is wrong for the 10 MHz path - it moves the trigger off the zero crossing and turns amplitude into phase - but it is right here: a pps is a rare, fast, possibly noisy edge on a long cable, which is the chatter case hysteresis exists for. No self-bias: a S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
THE SAMPLING FLIP-FLOP (FF1) IS DELIBERATELY ALLOWED TO GO METASTABLE - that is measurement. Never put a synchronizer in front of it. THE RETIMER (FF2) re-clocks on the next helper edge, so what leaves the board is always a clean transition aligned to a helper edge. It costs exactly one helper cycl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
DC-COUPLED, DELIBERATELY. The pps widths in this inventory span 1 us (FE-5680A) to 100 ms (ZED-F9T, LBE-1421), and no single AC-coupling RC covers five decades: a 10n/100k network passes the 1 us pulse and droops away to nothing 1% into the 100 ms one. The 1k/10k divider is fitted on EVERY pps chan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

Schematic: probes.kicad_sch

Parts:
C6001: 100n; C_0805_2012Metric
C6002: 10n; C_0805_2012Metric
D6001: PESD5V0S1BA; D_SOD-323; LCSC C2827694
J6001: PROBE 1; TerminalBlock_Phoenix_PT-1,5-3-3.5-H_1x03_P3.50mm_Horizontal; LCSC C880555
J6002: PROBE 2; TerminalBlock_Phoenix_PT-1,5-3-3.5-H_1x03_P3.50mm_Horizontal; LCSC C880555
J6003: PROBE 3; TerminalBlock_Phoenix_PT-1,5-3-3.5-H_1x03_P3.50mm_Horizontal; LCSC C880555
J6004: PROBE 4; TerminalBlock_Phoenix_PT-1,5-3-3.5-H_1x03_P3.50mm_Horizontal; LCSC C880555
J6005: PROBE 5; TerminalBlock_Phoenix_PT-1,5-3-3.5-H_1x03_P3.50mm_Horizontal; LCSC C880555
R6001: 22R; R_0805_2012Metric
R6002, R6004, R6006, R6008, R6010: 47R; R_1206_3216Metric
R6003, R6005, R6007, R6009, R6011: 47R; R_0805_2012Metric
R6051: 4R7; R_0805_2012Metric
TP6001: TP_1W; TestPoint_Pad_D1.5mm
U6001: DS2482S-100; SOIC-8_3.9x4.9mm_P1.27mm; LCSC C143306

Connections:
+3V3_D: R6002.1, R6004.1, R6006.1, R6008.1, R6010.1, R6051.1; also elsewhere on the board
GND: C6001.2, C6002.2, D6001.1 (A1), J6001.3, J6002.3, J6003.3, J6004.3, J6005.3, U6001.3 (GND), U6001.7 (AD1), U6001.8 (AD0); also elsewhere on the board
I2C_SCL: U6001.4 (SCL); also elsewhere on the board
I2C_SDA: U6001.5 (SDA); also elsewhere on the board
unnamed: J6001.1, R6003.2
unnamed: J6001.2, R6002.2
unnamed: J6002.1, R6005.2
unnamed: J6002.2, R6004.2
unnamed: J6003.1, R6007.2
unnamed: J6003.2, R6006.2
unnamed: J6004.1, R6009.2
unnamed: J6004.2, R6008.2
unnamed: J6005.1, R6011.2
unnamed: J6005.2, R6010.2
unnamed: R6001.1, U6001.2 (IO)
unnamed: C6001.1, C6002.1, R6051.2, U6001.1 (VCC)
ONEWIRE: D6001.2 (A2), R6001.2, R6003.1, R6005.1, R6007.1, R6009.1, R6011.1, TP6001.1; also elsewhere on the board

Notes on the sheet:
2 VCC probe RED
3 GND probe BLACK
1 DAT probe YELLOW
FIVE PROBES, ONE TERMINAL EACH no daisy chain, so a 5-way star
Five DROK DS18B20 probes, three wires each, one screw terminal each. I2C-to-1-Wire bridge at 0x18, so none of this costs a header pin.
AD1 = AD0 = 0 -> 0x18
1-WIRE TEMPERATURE PROBES
I2C TO 1-WIRE BRIDGE DS2482S-100, 0x18
PCTLZ open: the strong pullup is for
parasite-powered parts; ours get their own Vcc
ADDRESSING IS NOT POSITIONAL, AND THAT MATTERS ON THE BENCH. The bridge is at I2C 0x18. The five probes have NO addresses to set: each DS18B20 carries a unique 64-bit ROM code lasered in at the factory, and the DS2482's ROM Search walks the bus and finds all five. So five on one bus is always elect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
WHY EVERY BRANCH HAS TWO 47R, AND WHAT DECIDES WHETHER FIVE IN PARALLEL ACTUALLY WORK. THE BINDING LIMIT IS CAPACITANCE, NOT RESISTANCE. DS2482 datasheet note 2: at STANDARD speed the total 1-Wire bus capacitance must not exceed 1 nF, and at OVERDRIVE 300 pF. Budget: five DS18B20 DQ pins at their s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
